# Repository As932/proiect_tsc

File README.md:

# ⌚ Smartwatch Hardware Design - nRF52840

Acest repository conține documentația și fișierele de fabricație (Schematic, PCB Layout, BOM, Pick and Place, Gerbers) pentru un prototip de smartwatch ultra-low-power. Proiectul este construit în jurul ecosistemului Nordic Semiconductor și pune accent pe eficiența energetică extremă (standby de ordinul microamperilor) și pe o topologie PCB densă.

---

## 🛠️ 1. Arhitectura Hardware & Componente

Sistemul este împărțit în patru blocuri logice majore, conform schemei electrice:

### 1.1 Procesare & Conectivitate Radio
* **Microcontroller (MCU):** Nordic **nRF52840** (ARM® Cortex®-M4F la 64 MHz). Ales pentru consumul excelent în Deep Sleep și suportul nativ Bluetooth 5.0 Low Energy (BLE).
* **Cristal RTC:** 32.768 KHz (cu condensatoare de sarcină de 12pF) pentru menținerea timpului real cu un consum minim de energie.
* **Antenă:** Antenă ceramică SMD tip Chip, model **2450AT18B100E** (Johanson Technology), acompaniată de o rețea pasivă (Pi-matching network) pentru adaptarea impedanței la 2.4 GHz.

### 1.2 Interfață Utilizator (Afișaj)
* **Ecran E-Paper (e-Ink):** Conectat la PCB printr-un conector FPC cu 24 de pini (**503480-2400**).
* **Circuit de Boost E-Paper:** Panourile e-Ink necesită tensiuni specifice pentru acționarea stratului de cerneală. Placa include circuitul complet de comandă recomandat, folosind un inductor de **68uH** (L5) și diode Schottky **MBR0530** (D1, D2, D3), alături de condensatorii de filtraj asociați (10uF, 47uF).

### 1.3 Senzor de Mișcare
* **IMU (Inertial Measurement Unit):** Bosch **BMA423**. Este un accelerometru digital pe 3 axe optimizat special pentru *wearables*. Conține algoritmi hardware integrați (low-power) pentru numărarea pașilor (pedometru) și detectarea gesturilor (ex: *tilt-to-wake*), scutind MCU-ul de calcule complexe.

### 1.4 Power Management (Alimentare)
* **LiPo Charger:** **BQ25180YBGR**. Un IC dedicat managementului bateriilor mici de tip litiu-polimer. Oferă un control precis al curentului de încărcare (esențial pentru bateriile de smartwatch) și terminare sigură a ciclului de încărcare.
* **Regulator DC/DC Buck-Boost:** **RT6150AWSC**. Aceasta este o componentă critică a designului. Deoarece bateria LiPo variază de la 4.2V (plină) la 3.0V (goală), acest convertor menține tensiunea sistemului (VOUT) la un nivel stabil de 3.3V, trecând automat din modul *Buck* (coborâtor) în modul *Boost* (ridicător) pe măsură ce bateria se descarcă.

---

## 📌 2. Alocarea Pinilor nRF52840 (Interfețe)

Conexiunile fizice între MCU și periferice au fost rutate pentru a minimiza încrucișările și a asigura integritatea semnalelor.

| Componentă | Pin MCU | Interfață / Rol | Justificare & Funcționalitate |
| :--- | :---: | :---: | :--- |
| **BMA423 (IMU)** | `[P0.06]` | I2C (SDA) | Magistrală de comunicație date. |
| **BMA423 (IMU)** | `[P0.07]` | I2C (SCL) | Magistrală de clock (SCL). BMA423 lucrează ca slave I2C. |
| **BMA423 (IMU)** | `[P0.08, P1.08]` | INT | Pin de interrupt hardware. Trezește MCU-ul când detectează o mișcare a încheieturii. |
| **E-Paper (EPD)** | `[P0.03]` | SPI (MOSI) | Magistrala SPI rapidă pentru trimiterea frame-buffer-ului (imaginii) către ecran. |
| **E-Paper (EPD)** | `[P0.02]` | SPI (SCK) | Clock pentru magistrala SPI. |
| **E-Paper (EPD)** | `[P0.17]` | GPIO (BUSY) | Pin de stare (Input). MCU-ul intră în sleep și așteaptă ca acest pin să semnalizeze terminarea refresh-ului fizic al ecranului. |
| **SWD / Debug** | N/A | SWDIO / SWDCLK | Programarea se face via un conector de suprafață **TC2030-IDC** (Tag-Connect) cu 6 pad-uri, economisind masiv spațiu pe placă. |

---

## 🔋 3. Analiza Consumului de Energie (Power Budget Estimativ)

Ecosistemul hardware a fost ales pentru a maximiza autonomia unei baterii de capacitate redusă (ex: 150-200 mAh).

1.  **Standby / Deep Sleep (Regim majoritar):** * nRF52840 (RTC activ) + BMA423 (Low-power mode) + RT6150 (Quiescent) = **Aprox. 5 - 10 µA**.
    * *E-Paper-ul consumă 0 µA pentru a menține imaginea afișată.*
2.  **Evenimente Active (Scurte):**
    * **Refresh Ecran:** Curentul absorbit de circuitul de boost este de **aprox. 8 - 15 mA** timp de ~1-2 secunde, doar în momentul actualizării.
    * **Transmisie BLE:** Vârfuri scurte de curent (Tx Peak) la transmiterea pachetelor radio.
3.  **Concluzie:** Curentul mediu de descărcare este dominat de cât de des se actualizează ecranul (ex: la minut vs. la secundă) și de cât de des se sincronizează Bluetooth-ul. Într-un regim optimizat de ceas de mână, hardware-ul permite funcționarea de ordinul săptămânilor.

---

## 📐 4. Design Log & Integrare Mecanică

### Layout PCB & Integritate Electromagnetică
* **Planuri de Masă & Via Stitching:** Pentru a ecrana zgomotul (EMI) și a asigura un nivel de referință stabil pentru circuitul RF (Antenă), placa dispune de planuri de masă (`GND`) solide pe ambele straturi (TOP și BOTTOM). Acestea sunt cusute între ele (Via Stitching) pe toată suprafața disponibilă.
* **Zona RF:** S-a creat un *Polygon Cutout* (zonă liberă de cupru) strict sub și în jurul antenei ceramice 2450AT18B100E pentru a nu ecrana și a nu dezacorda propagarea undelor de 2.4 GHz.
* **Necking Down pe Alimentare:** Traseele de putere au fost rutate pe cât posibil cu o lățime de 0.3mm. Totuși, în zonele foarte congestionate (în proximitatea PMIC-ului BQ25180 și a procesorului), traseele au fost îngustate local (*neck-down*) pentru a permite amplasarea condensatorilor de decuplare (ex: C38, C39) cât mai aproape de pini.

### Status Integrare 3D & Carcasă (Mechanical)
1. **Modelul Nativ:** Fișierul `.f3z` din folderul *Mechanical* conține designul nativ din Fusion 360 al plăcii. Au fost rezolvate erorile vizuale de extrudare a pachetelor lipsă (cărămizile negre) specifice componentelelor custom.
2. **Exploded View (WIP):** Etapa de asamblare este în desfășurare. S-a realizat exportul plăcii (Switch to 3D PCB). Amplasarea conceptuală a dispozitivului urmează un design tip "sandwich":
   * **Bateria:** Plasată sub PCB (pe fața BOTTOM).
   * **Ecranul E-Paper:** Poziționat deasupra PCB-ului (pe fața TOP), conectat prin cablul FPC îndoit.
   * *Notă:* Modelele 3D exacte pentru baterie și display urmează să fie importate și aliniate pentru exportul final de ansamblu tip `.step`.

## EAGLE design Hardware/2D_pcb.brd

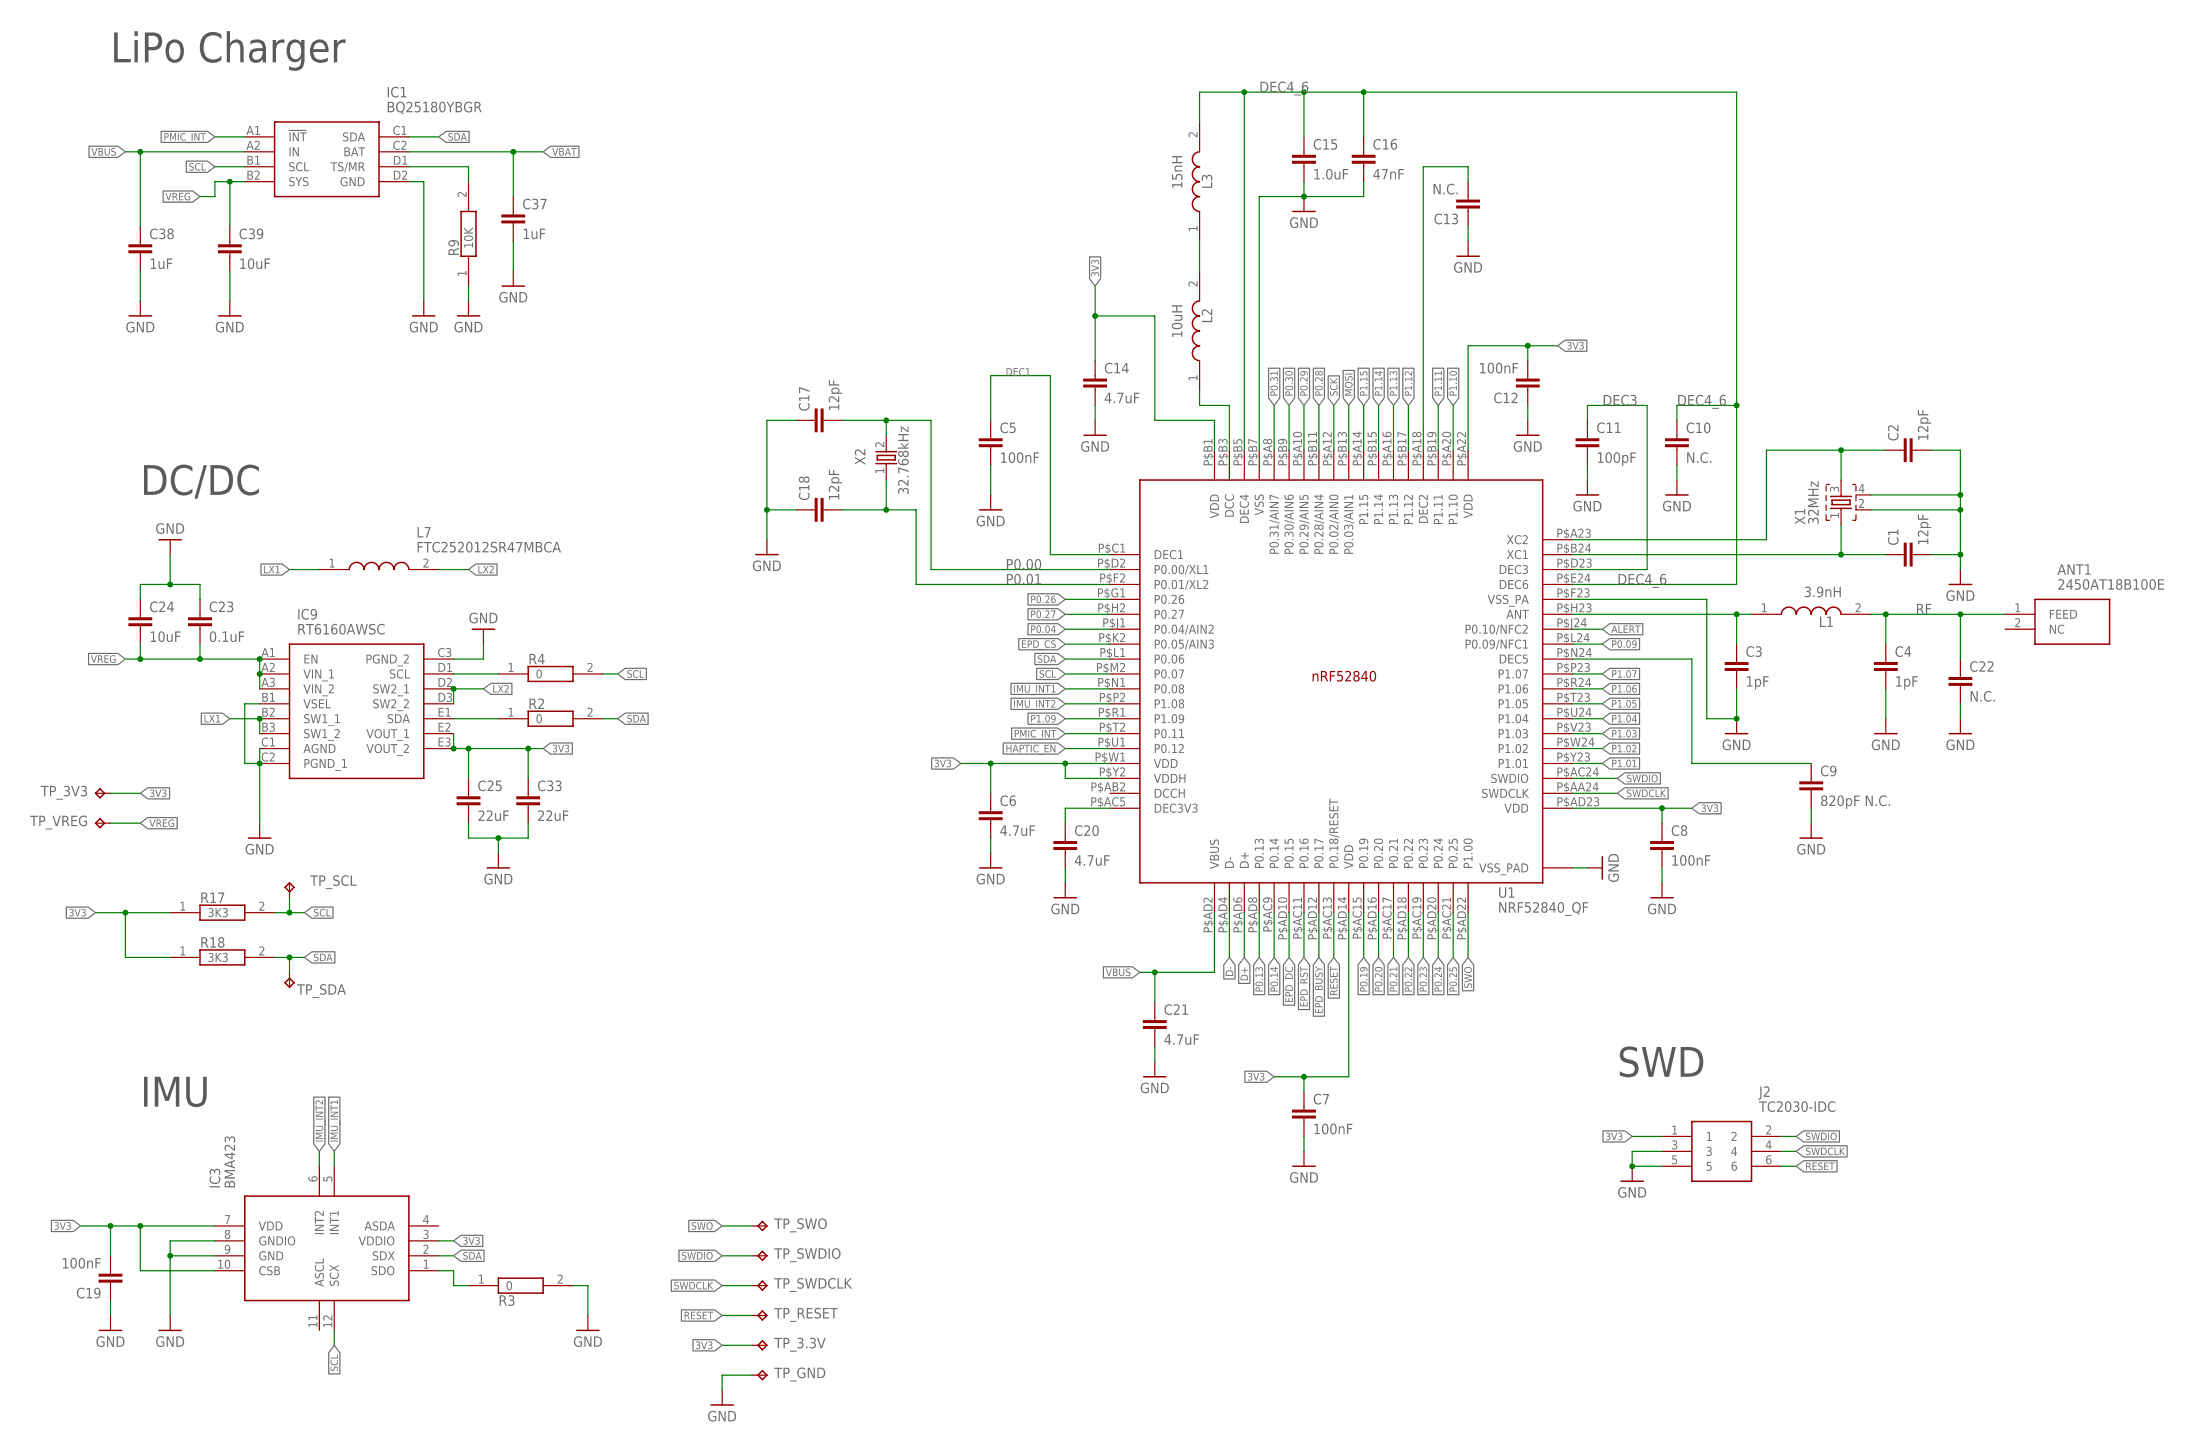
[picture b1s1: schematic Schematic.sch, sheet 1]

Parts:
ANT1: 2450AT18B100E; 2450AT18B100E_ANTC3216X140N
C1, C2, C17, C18: 12pF; NORDIC_NRF_3_RESC0201_N
C3, C4: 1pF; NORDIC_NRF_3_RESC0201_N
C5, C7, C8, C12, C19: 100nF; NORDIC_NRF_3_RESC0201_N
C6, C14, C20, C21: 4.7uF; NORDIC_NRF_3_RESC0402_N
C9: 820pF N.C.; NORDIC_NRF_3_RESC0201_N
C10, C13, C22: N.C.; NORDIC_NRF_3_RESC0201_N
C11: 100pF; NORDIC_NRF_3_RESC0201_N
C15: 1.0uF; NORDIC_NRF_3_RESC0402_N
C16: 47nF; NORDIC_NRF_3_RESC0201_N
C23: 0.1uF; NORDIC_NRF_3_RESC0201_N
C24, C39: 10uF; NORDIC_NRF_3_RESC0402_N
C25, C33: 22uF; NORDIC_NRF_3_RESC0402_N
C37, C38: 1uF; NORDIC_NRF_3_RESC0402_N
IC1: BQ25180YBGR; BQ25180YBGR_BGA8C40P2X4_100X155X50
IC3: BMA423; BMA423_BMA423
IC9: RT6160AWSC; RT6160AWSC_BGA15C40P3X5_140X230X60
J2: TC2030-IDC; TC2030-IDC_TC2030IDC
L1: 3.9nH; MLP2016SR47MT0S1_INDC2016X100N
L2: 10uH; MLP2016SR47MT0S1_INDC2016X100N
L3: 15nH; MLP2016SR47MT0S1_INDC2016X100N
L7: FTC252012SR47MBCA; MLP2016SR47MT0S1_INDC2016X100N
R2, R3, R4: 0; CPF0201D7K68C1_0201
R9: 10K; CPF0201D7K68C1_0201
R17, R18: 3K3; CPF0201D7K68C1_0201
TP_3.3V, TP_3V3: HECTOR_WATCH_1_TPTP20R; HECTOR_WATCH_1_TP20R
TP_GND: HECTOR_WATCH_1_TPTP20R; HECTOR_WATCH_1_TP20R
TP_RESET: HECTOR_WATCH_1_TPTP20R; HECTOR_WATCH_1_TP20R
TP_SCL: HECTOR_WATCH_1_TPTP20R; HECTOR_WATCH_1_TP20R
TP_SDA: HECTOR_WATCH_1_TPTP20R; HECTOR_WATCH_1_TP20R
TP_SWDCLK: HECTOR_WATCH_1_TPTP20R; HECTOR_WATCH_1_TP20R
TP_SWDIO: HECTOR_WATCH_1_TPTP20R; HECTOR_WATCH_1_TP20R
TP_SWO: HECTOR_WATCH_1_TPTP20R; HECTOR_WATCH_1_TP20R
TP_VREG: HECTOR_WATCH_1_TPTP20R; HECTOR_WATCH_1_TP20R
U1: NRF52840_QF; NORDIC_NRF_4_AQFN50P700X700X85_HS-74N
X1: 32MHz; NORDIC_NRF_BT-XTAL_2016_N
X2: 32.768kHz; NORDIC_NRF_1_XTAL_3215_N

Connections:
3V3: C6.1, C7.1, C8.1, C12.2, C14.1, C19.2, C25.1, C33.1, IC3.3 (VDDIO), IC3.7 (VDD), IC3.10 (CSB), IC9.E2 (VOUT_1), IC9.E3 (VOUT_2), J2.1, R17.1, R18.1, TP_3.3V.TP, TP_3V3.TP, U1.P$A22 (VDD), U1.P$AD14 (VDD), U1.P$AD23 (VDD), U1.P$B1 (VDD), U1.P$W1 (VDD), U1.P$Y2 (VDDH); also elsewhere on the board
ALERT: U1.P$J24 (P0.10/NFC2); also elsewhere on the board
D+: U1.P$AD6 (D+); also elsewhere on the board
D-: U1.P$AD4 (D-); also elsewhere on the board
DEC1: C5.1, U1.P$C1 (DEC1)
DEC3: C11.1, U1.P$D23 (DEC3)
DEC4_6: C10.1, C15.1, C16.1, L3.2, U1.P$B5 (DEC4), U1.P$E24 (DEC6)
EPD_BUSY: U1.P$AD12 (P0.17); also elsewhere on the board
EPD_CS: U1.P$K2 (P0.05/AIN3); also elsewhere on the board
EPD_DC: U1.P$AD10 (P0.15); also elsewhere on the board
EPD_RST: U1.P$AC11 (P0.16); also elsewhere on the board
GND: C1.2, C2.2, C3.2, C4.2, C5.2, C6.2, C7.2, C8.2, C9.2, C10.2, C11.2, C12.1, C13.1, C14.2, C15.2, C16.2, C17.1, C18.1, C19.1, C20.2, C21.2, C22.2, C23.1, C24.1, C25.2, C33.2, C37.2, C38.2, C39.2, IC1.D2 (GND), IC3.8 (GNDIO), IC3.9 (GND), IC9.B1 (VSEL), IC9.C1 (AGND), IC9.C2 (PGND_1), IC9.C3 (PGND_2), J2.3, J2.5, R3.2, R9.1, TP_GND.TP, U1.P$74 (VSS_PAD), U1.P$75 (VSS_PAD), U1.P$76 (VSS_PAD), U1.P$77 (VSS_PAD), U1.P$78 (VSS_PAD), U1.P$79 (VSS_PAD), U1.P$80 (VSS_PAD), U1.P$81 (VSS_PAD), U1.P$82 (VSS_PAD), U1.P$83 (VSS_PAD), U1.P$84 (VSS_PAD), U1.P$85 (VSS_PAD), U1.P$86 (VSS_PAD), U1.P$87 (VSS_PAD), U1.P$88 (VSS_PAD), U1.P$89 (VSS_PAD), U1.P$90 (VSS_PAD), U1.P$B7 (VSS), U1.P$F23 (VSS_PA), X1.2, X1.4; also elsewhere on the board
HAPTIC_EN: U1.P$U1 (P0.12); also elsewhere on the board
IMU_INT1: IC3.5 (INT1), U1.P$N1 (P0.08)
IMU_INT2: IC3.6 (INT2), U1.P$P2 (P1.08)
LX1: IC9.B2 (SW1_1), IC9.B3 (SW1_2), L7.1
LX2: IC9.D2 (SW2_1), IC9.D3 (SW2_2), L7.2
MOSI: U1.P$B13 (P0.03/AIN1); also elsewhere on the board
unnamed: IC1.D1 (TS/MR), R9.2
unnamed: IC9.D1 (SCL), R4.1
unnamed: IC9.E1 (SDA), R2.1
unnamed: IC3.1 (SDO), R3.1
unnamed: C20.1, U1.P$AC5 (DEC3V3)
unnamed: L2.1, U1.P$B3 (DCC)
unnamed: L2.2, L3.1
unnamed: C13.2, U1.P$A18 (DEC2)
unnamed: C2.1, U1.P$A23 (XC2), X1.3
unnamed: C1.1, U1.P$B24 (XC1), X1.1
unnamed: C3.1, L1.1, U1.P$H23 (ANT)
unnamed: C9.1, U1.P$N24 (DEC5)
P0.00: C17.2, U1.P$D2 (P0.00/XL1), X2.2
P0.01: C18.2, U1.P$F2 (P0.01/XL2), X2.1
P0.04: U1.P$J1 (P0.04/AIN2)
P0.09: U1.P$L24 (P0.09/NFC1)
P0.13: U1.P$AD8 (P0.13); also elsewhere on the board
P0.14: U1.P$AC9 (P0.14); also elsewhere on the board
P0.19: U1.P$AC15 (P0.19)
P0.20: U1.P$AD16 (P0.20)
P0.21: U1.P$AC17 (P0.21)
P0.22: U1.P$AD18 (P0.22)
P0.23: U1.P$AC19 (P0.23)
P0.24: U1.P$AD20 (P0.24)
P0.25: U1.P$AC21 (P0.25)
P0.26: U1.P$G1 (P0.26)
P0.27: U1.P$H2 (P0.27)
P0.28: U1.P$B11 (P0.28/AIN4)
P0.29: U1.P$A10 (P0.29/AIN5)
P0.30: U1.P$B9 (P0.30/AIN6)
P0.31: U1.P$A8 (P0.31/AIN7)
P1.01: U1.P$Y23 (P1.01); also elsewhere on the board
P1.02: U1.P$W24 (P1.02); also elsewhere on the board
P1.03: U1.P$V23 (P1.03)
P1.04: U1.P$U24 (P1.04)
P1.05: U1.P$T23 (P1.05)
P1.06: U1.P$R24 (P1.06)
P1.07: U1.P$P23 (P1.07)
P1.09: U1.P$R1 (P1.09)
P1.10: U1.P$A20 (P1.10)
P1.11: U1.P$B19 (P1.11)
P1.12: U1.P$B17 (P1.12)
P1.13: U1.P$A16 (P1.13)
P1.14: U1.P$B15 (P1.14)
P1.15: U1.P$A14 (P1.15)
PMIC_INT: IC1.A1 (!INT), U1.P$T2 (P0.11)
RESET: J2.6, TP_RESET.TP, U1.P$AC13 (P0.18/RESET)
RF: ANT1.1 (FEED), C4.1, C22.1, L1.2
SCK: U1.P$A12 (P0.02/AIN0); also elsewhere on the board
SCL: IC1.B1 (SCL), IC3.12 (SCX), R4.2, R17.2, TP_SCL.TP, U1.P$M2 (P0.07); also elsewhere on the board
SDA: IC1.C1 (SDA), IC3.2 (SDX), R2.2, R18.2, TP_SDA.TP, U1.P$L1 (P0.06); also elsewhere on the board
SWDCLK: J2.4, TP_SWDCLK.TP, U1.P$AA24 (SWDCLK)
SWDIO: J2.2, TP_SWDIO.TP, U1.P$AC24 (SWDIO)
SWO: TP_SWO.TP, U1.P$AD22 (P1.00)
VBAT: C37.1, IC1.C2 (BAT); also elsewhere on the board
VBUS: C21.1, C38.1, IC1.A2 (IN), U1.P$AD2 (VBUS); also elsewhere on the board
VREG: C23.2, C24.2, C39.1, IC1.B2 (SYS), IC9.A1 (EN), IC9.A2 (VIN_1), IC9.A3 (VIN_2), TP_VREG.TP

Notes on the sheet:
LiPo Charger
DC/DC
IMU
SWD

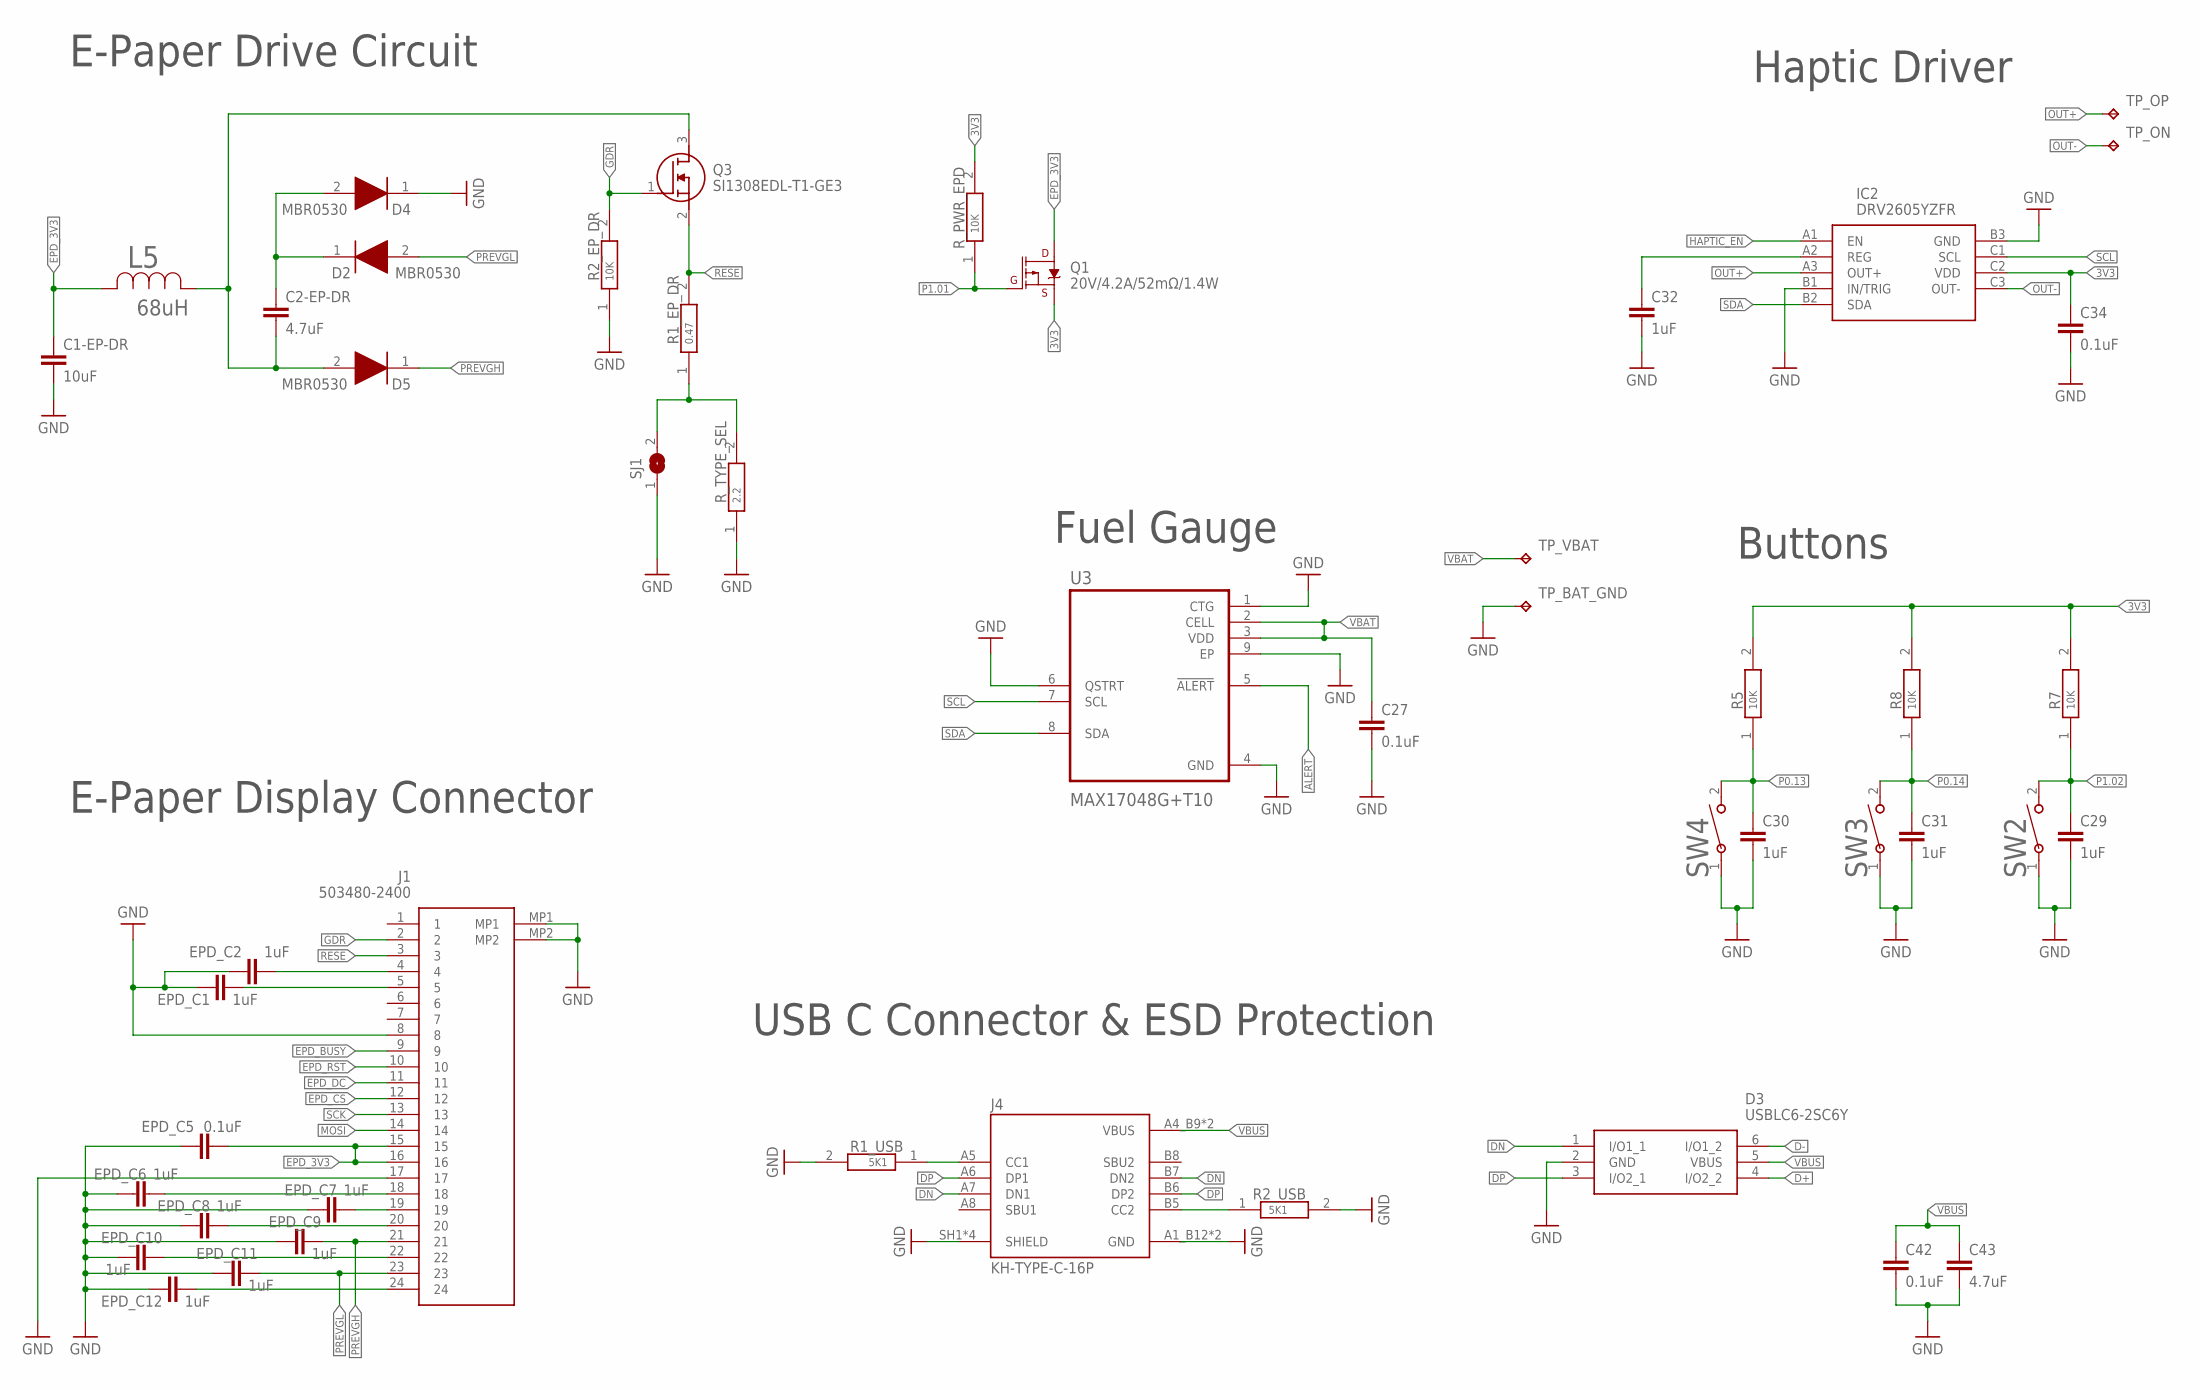
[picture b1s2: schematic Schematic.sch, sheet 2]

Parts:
C1-EP-DR: 10uF; NORDIC_NRF_3_RESC0402_N
C2-EP-DR, C43: 4.7uF; NORDIC_NRF_3_RESC0402_N
C27, C34, C42: 0.1uF; NORDIC_NRF_3_RESC0201_N
C29, C30, C31, C32: 1uF; NORDIC_NRF_3_RESC0402_N
D2, D4, D5: MBR0530; ESP32_C6_LIBRARY_5_SOD3716X135N
D3: USBLC6-2SC6Y; ESP32_C6_LIBRARY_3_SOT95P280X145-6N
EPD_C1, EPD_C2, EPD_C6, EPD_C7, EPD_C8, EPD_C9, EPD_C10, EPD_C11, EPD_C12: 1uF; NORDIC_NRF_3_RESC0402_N
EPD_C5: 0.1uF; NORDIC_NRF_3_RESC0201_N
IC2: DRV2605YZFR; DRV2605YZFR_BGA9C50P3X3_144X144X62
J1: 503480-2400; 503480-2400_5034802400
J4: KH-TYPE-C-16P; KH-TYPE-C-16P_KINGHELM_KH-TYPE-C-16P
L5: 68uH; ESP32_C6_LIBRARY_2_IND_4828-WE-TPC_WRE
Q1: 20V/4.2A/52mΩ/1.4W; ESP32_C6_LIBRARY_4_ESP32_C6_LIBRARY_4_ESP32_C6_LIBRARY_4_ES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
Q3: SI1308EDL-T1-GE3; ESP32_C6_LIBRARY_6_SOT65P210X110-3N
R1_EP_DR: 0.47; CPF0201D7K68C1_0201
R1_USB, R2_USB: 5K1; CPF0201D7K68C1_0201
R2_EP_DR, R5, R7, R8: 10K; CPF0201D7K68C1_0201
R_PWR_EPD: 10K; CPF0201D7K68C1_0201
R_TYPE_SEL: 2.2; CPF0201D7K68C1_0201
SJ1: ESP32_C6_LIBRARY_7_JUMPER_SJ
SW2, SW3, SW4: 0; 2025-10-22_07-23-44_LIBRARY_SW_EVP-AKE31A_PAN
TP_BAT_GND: HECTOR_WATCH_1_TPTP20R; HECTOR_WATCH_1_TP20R
TP_ON: HECTOR_WATCH_1_TPTP20R; HECTOR_WATCH_1_TP20R
TP_OP: HECTOR_WATCH_1_TPTP20R; HECTOR_WATCH_1_TP20R
TP_VBAT: HECTOR_WATCH_1_TPTP20R; HECTOR_WATCH_1_TP20R
U3: MAX17048G+T10; ESP32_C6_LIBRARY_SON50P200X200X80-9N

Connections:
3V3: C34.1, IC2.C2 (VDD), Q1.2 (S), R5.2, R7.2, R8.2, R_PWR_EPD.2; also elsewhere on the board
ALERT: U3.5 (!ALERT); also elsewhere on the board
D+: D3.4 (I/O2_2); also elsewhere on the board
D-: D3.6 (I/O1_2); also elsewhere on the board
DN: D3.1 (I/O1_1), J4.A7 (DN1), J4.B7 (DN2)
DP: D3.3 (I/O2_1), J4.A6 (DP1), J4.B6 (DP2)
EPD_3V3: C1-EP-DR.1, EPD_C5.2, J1.15, J1.16, L5.2, Q1.3 (D)
EPD_BUSY: J1.9; also elsewhere on the board
EPD_CS: J1.12; also elsewhere on the board
EPD_DC: J1.11; also elsewhere on the board
EPD_RST: J1.10; also elsewhere on the board
GDR: J1.2, Q3.1 (G), R2_EP_DR.2
GND: C1-EP-DR.2, C27.2, C29.2, C30.2, C31.2, C32.2, C34.2, C42.2, C43.2, D3.2 (GND), D4.1 (K), EPD_C1.1, EPD_C2.1, EPD_C5.1, EPD_C6.1, EPD_C7.1, EPD_C8.1, EPD_C9.1, EPD_C10.1, EPD_C11.1, EPD_C12.1, IC2.B1 (IN/TRIG), IC2.B3 (GND), J1.8, J1.17, J1.MP1, J1.MP2, J4.A1_B12 (GND), J4.A12_B1 (GND), J4.SH1 (SHIELD), J4.SH2 (SHIELD), J4.SH3 (SHIELD), J4.SH4 (SHIELD), R1_USB.2, R2_EP_DR.1, R2_USB.2, R_TYPE_SEL.1, SJ1.1, SW2.1, SW3.1, SW4.1, TP_BAT_GND.TP, U3.1 (CTG), U3.4 (GND), U3.6 (QSTRT), U3.9 (EP); also elsewhere on the board
HAPTIC_EN: IC2.A1 (EN); also elsewhere on the board
MOSI: J1.14; also elsewhere on the board
unnamed: C2-EP-DR.1, D2.1 (K), D4.2 (A)
unnamed: C2-EP-DR.2, D5.2 (A), L5.1, Q3.3 (D)
unnamed: R1_EP_DR.1, R_TYPE_SEL.2, SJ1.2
unnamed: EPD_C1.2, J1.5
unnamed: EPD_C2.2, J1.4
unnamed: EPD_C6.2, J1.18
unnamed: EPD_C7.2, J1.19
unnamed: EPD_C8.2, J1.20
unnamed: C32.1, IC2.A2 (REG)
unnamed: EPD_C10.2, J1.22
unnamed: J4.B5 (CC2), R2_USB.1
unnamed: EPD_C12.2, J1.24
unnamed: J4.A5 (CC1), R1_USB.1
OUT+: IC2.A3 (OUT+), TP_OP.TP
OUT-: IC2.C3 (OUT-), TP_ON.TP
P0.13: C30.1, R5.1, SW4.2; also elsewhere on the board
P0.14: C31.1, R8.1, SW3.2; also elsewhere on the board
P1.01: Q1.1 (G), R_PWR_EPD.1; also elsewhere on the board
P1.02: C29.1, R7.1, SW2.2; also elsewhere on the board
PREVGH: D5.1 (K), EPD_C9.2, J1.21
PREVGL: D2.2 (A), EPD_C11.2, J1.23
RESE: J1.3, Q3.2 (S), R1_EP_DR.2
SCK: J1.13; also elsewhere on the board
SCL: IC2.C1 (SCL), U3.7 (SCL); also elsewhere on the board
SDA: IC2.B2 (SDA), U3.8 (SDA); also elsewhere on the board
VBAT: C27.1, TP_VBAT.TP, U3.2 (CELL), U3.3 (VDD); also elsewhere on the board
VBUS: C42.1, C43.1, D3.5 (VBUS), J4.A4_B9 (VBUS), J4.A9_B4 (VBUS); also elsewhere on the board

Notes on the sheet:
E-Paper Drive Circuit
E-Paper Display Connector
Fuel Gauge
Haptic Driver
Buttons
USB C Connector & ESD Protection

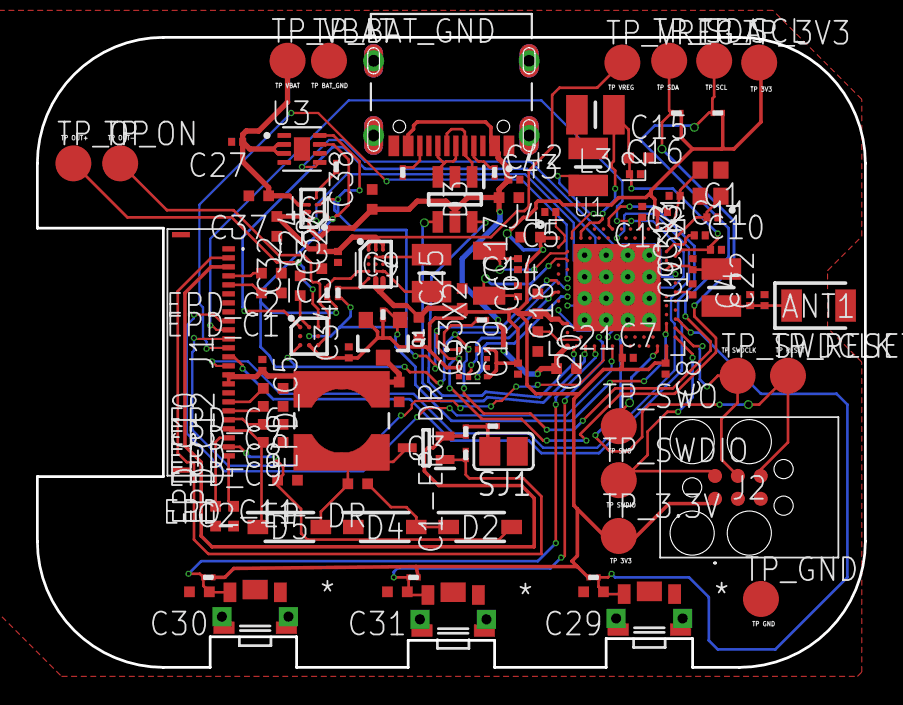
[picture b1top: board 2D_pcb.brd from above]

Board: 4 copper layers, 46.0 x 35.0 mm, 105 parts (0 on the bottom side), 70 nets.

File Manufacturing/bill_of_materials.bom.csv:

Reference Designators;Quantity;Description;Package;Value;Manufacturer;Manufacturer Part Number;Vendor;Vendor Part Number;Top/Bottom;
;1;Board;Board;;;;;;;
ANT1;1;Antennas 2.45GHz ANTENNA;2450AT18B100E_ANTC3216X140N;2450AT18B100E;;;;;Top;
C1-EP-DR, C24, C39;3;Generic chip capacitor;NORDIC_NRF_3_RESC0402_N;10uF;;;;;Top;
C1, C2, C17, C18;4;Generic chip capacitor;NORDIC_NRF_3_RESC0201_N;12pF;;;;;Top;
C2-EP-DR, C6, C14, C20, C21, C43;6;Generic chip capacitor;NORDIC_NRF_3_RESC0402_N;4.7uF;;;;;Top;
C3, C4;2;Generic chip capacitor;NORDIC_NRF_3_RESC0201_N;1pF;;;;;Top;
C5, C7, C8, C12, C19;5;Generic chip capacitor;NORDIC_NRF_3_RESC0201_N;100nF;;;;;Top;
C9;1;Generic chip capacitor;NORDIC_NRF_3_RESC0201_N;820pF N.C.;;;;;Top;
C10, C13, C22;3;Generic chip capacitor;NORDIC_NRF_3_RESC0201_N;N.C.;;;;;Top;
C11;1;Generic chip capacitor;NORDIC_NRF_3_RESC0201_N;100pF;;;;;Top;
C15;1;Generic chip capacitor;NORDIC_NRF_3_RESC0402_N;1.0uF;;;;;Top;
C16;1;Generic chip capacitor;NORDIC_NRF_3_RESC0201_N;47nF;;;;;Top;
C23, C27, C34, C42, EPD_C5;5;Generic chip capacitor;NORDIC_NRF_3_RESC0201_N;0.1uF;;;;;Top;
C25, C33;2;Generic chip capacitor;NORDIC_NRF_3_RESC0402_N;22uF;;;;;Top;
C29, C30, C31, C32, C37, C38, EPD_C1, EPD_C2, EPD_C6, EPD_C7, EPD_C8, EPD_C9, EPD_C10, EPD_C11, EPD_C12;15;Generic chip capacitor;NORDIC_NRF_3_RESC0402_N;1uF;;;;;Top;
D2, D4, D5;3;ON SEMICONDUCTOR - MBR0530 - DIODE, SCHOTTKY, 0.5A, 30V, SOD-123;SOD3716X135N;MBR0530;;;;;Top;
D3;1;Low Cap. ESD Protection Auto SOT-23-6 STMicroelectronics USBLC6-2SC6Y, Dual Uni-Directional TVS Diode Array, 6-Pin SOT-23;SOT95P280X145-6N;USBLC6-2SC6Y;;;;;Top;
IC1;1;Charger IC Lithium Ion/Polymer, Lithium Iron Phosphate 8-DSBGA (1.6x1.1);BQ25180YBGR_BGA8C40P2X4_100X155X50;BQ25180YBGR;;;;;Top;
IC2;1;Haptic Driver for ERM/LRA with Built-In Library and Smart Loop Architecture;DRV2605YZFR_BGA9C50P3X3_144X144X62;DRV2605YZFR;;;;;Top;
IC3;1;Accelerometers Triaxial low-g 12bit Acceleration Sensor;BMA423_BMA423;BMA423;;;;;Top;
IC9;1;Buck-Boost Regulator Positive Output Step-Up/Step-Down I2C DC-DC Controller IC 15-WL-CSP (BSC) (1.4x2.3);RT6160AWSC_BGA15C40P3X5_140X230X60;RT6160AWSC;;;;;Top;
J1;1;FFC & FPC Connectors 0.5mm FPC RA SMT Dual Contact 24Ckt;503480-2400_5034802400;503480-2400;;;;;Top;
J2;1;CABLE ADAPTER 6 POS;TC2030-IDC_TC2030IDC;TC2030-IDC;;;;;Top;
J4;1;Check availability;KINGHELM_KH-TYPE-C-16P;KH-TYPE-C-16P;;;;;Top;
L1;1;SMD / SMT Inductors (Coils), L=0.47?H, L x W x T :;MLP2016SR47MT0S1_INDC2016X100N;3.9nH;;;;;Top;
L2;1;SMD / SMT Inductors (Coils), L=0.47?H, L x W x T :;MLP2016SR47MT0S1_INDC2016X100N;10uH;;;;;Top;
L3;1;SMD / SMT Inductors (Coils), L=0.47?H, L x W x T :;MLP2016SR47MT0S1_INDC2016X100N;15nH;;;;;Top;
L5;1;;ESP32_C6_LIBRARY_2_IND_4828-WE-TPC_WRE;68uH;;;;;Top;
L7;1;SMD / SMT Inductors (Coils), L=0.47?H, L x W x T :;MLP2016SR47MT0S1_INDC2016X100N;FTC252012SR47MBCA;;;;;Top;
Q1;1;P-channel MOSFETs;ESP32_WROVER_SPARKFUN-DISCRETESEMI_SOT23-3;20V/4.2A/52mΩ/1.4W;;;;;Top;
Q3;1;MOSFET N-Ch 30V 1.5A TrenchFET SC70 Vishay Si1308EDL-T1-GE3 N-channel MOSFET Transistor, 1.5 A, 30 V, 3-Pin SC-70;SOT65P210X110-3N;SI1308EDL-T1-GE3;;;;;Top;
R_PWR_EPD, R2_EP_DR, R5, R7, R8, R9;6;7.68k 0201 Thin Film Surface Mount Fixed Resistor +/-0.5% 0.031W CPF0201D7K68C1;CPF0201D7K68C1_0201;10K;;;;;Top;
R_TYPE_SEL;1;7.68k 0201 Thin Film Surface Mount Fixed Resistor +/-0.5% 0.031W CPF0201D7K68C1;CPF0201D7K68C1_0201;2.2;;;;;Top;
R1_EP_DR;1;7.68k 0201 Thin Film Surface Mount Fixed Resistor +/-0.5% 0.031W CPF0201D7K68C1;CPF0201D7K68C1_0201;0.47;;;;;Top;
R1_USB, R2_USB;2;7.68k 0201 Thin Film Surface Mount Fixed Resistor +/-0.5% 0.031W CPF0201D7K68C1;CPF0201D7K68C1_0201;5K1;;;;;Top;
R2, R3, R4;3;7.68k 0201 Thin Film Surface Mount Fixed Resistor +/-0.5% 0.031W CPF0201D7K68C1;CPF0201D7K68C1_0201;0;;;;;Top;
R17, R18;2;7.68k 0201 Thin Film Surface Mount Fixed Resistor +/-0.5% 0.031W CPF0201D7K68C1;CPF0201D7K68C1_0201;3K3;;;;;Top;
SJ1;1;SMD solder JUMPER;JUMPER_SJ;;;;;;Top;
SW2, SW3, SW4;3;;SW_EVP-AKE31A_PAN;0;;;;;Top;
TP_3.3V, TP_3V3, TP_BAT_GND, TP_GND, TP_ON, TP_OP, TP_RESET, TP_SCL, TP_SDA, TP_SWDCLK, TP_SWDIO, TP_SWO, TP_VBAT, TP_VREG;14;Test pad;HECTOR_WATCH_1_TP20R;HECTOR_WATCH_1_TPTP20R;;;;;Top;
U1;1;nRF52840;NORDIC_NRF_4_AQFN50P700X700X85_HS-74N;NRF52840_QF;;;;;Top;
U3;1;Check availability;SON50P200X200X80-9N;MAX17048G+T10;;;;;Top;
X1;1;;NORDIC_NRF_BT-XTAL_2016_N;32MHz;;;;;Top;
X2;1;;NORDIC_NRF_1_XTAL_3215_N;32.768kHz;;;;;Top;

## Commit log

2026-04-10 Create empty
2026-04-20 Create LICENSE
2026-04-20 Add files via upload
    last v of schematic and 2d pcb
2026-04-20 Add files via upload
    added pdf file containing schematic

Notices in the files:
parts and their libraries:
COPYRIGHT: Copyright (C) 2024 Ultra Librarian. All rights reserved.
COPYRIGHT: Copyright (C) 2025 Ultra Librarian. All rights reserved.
